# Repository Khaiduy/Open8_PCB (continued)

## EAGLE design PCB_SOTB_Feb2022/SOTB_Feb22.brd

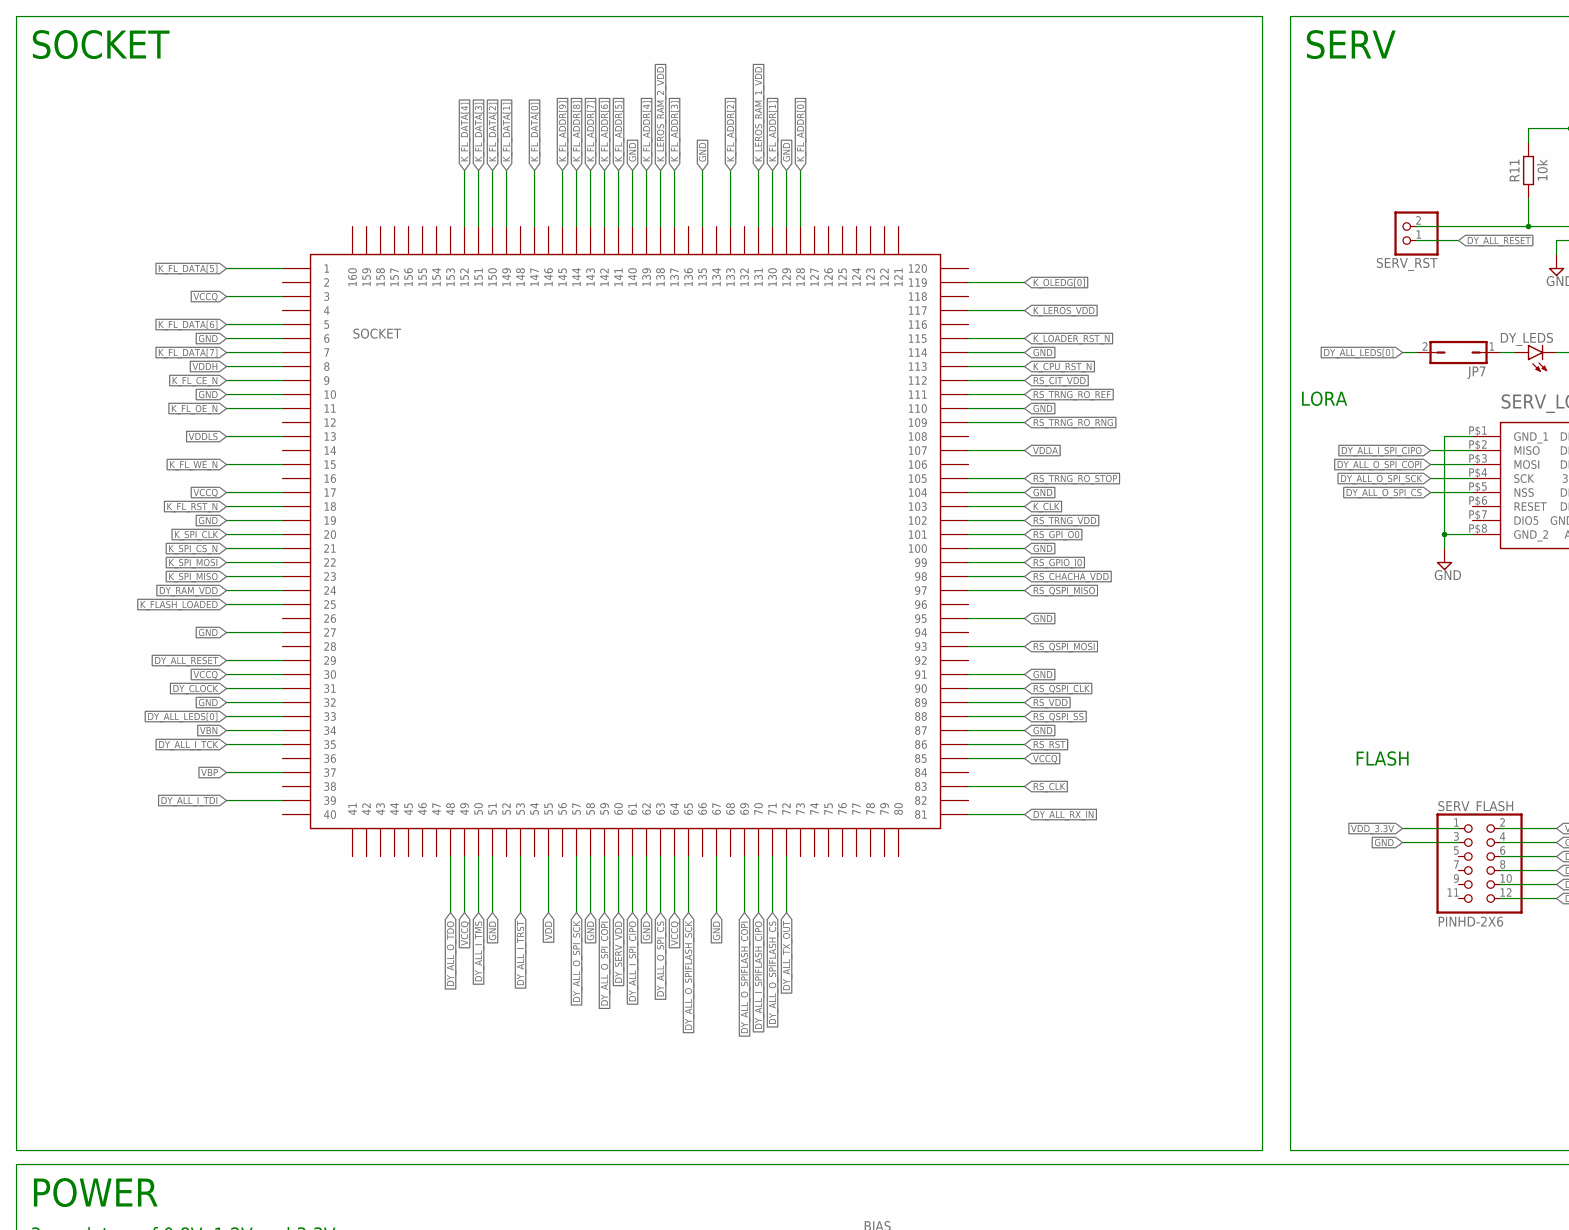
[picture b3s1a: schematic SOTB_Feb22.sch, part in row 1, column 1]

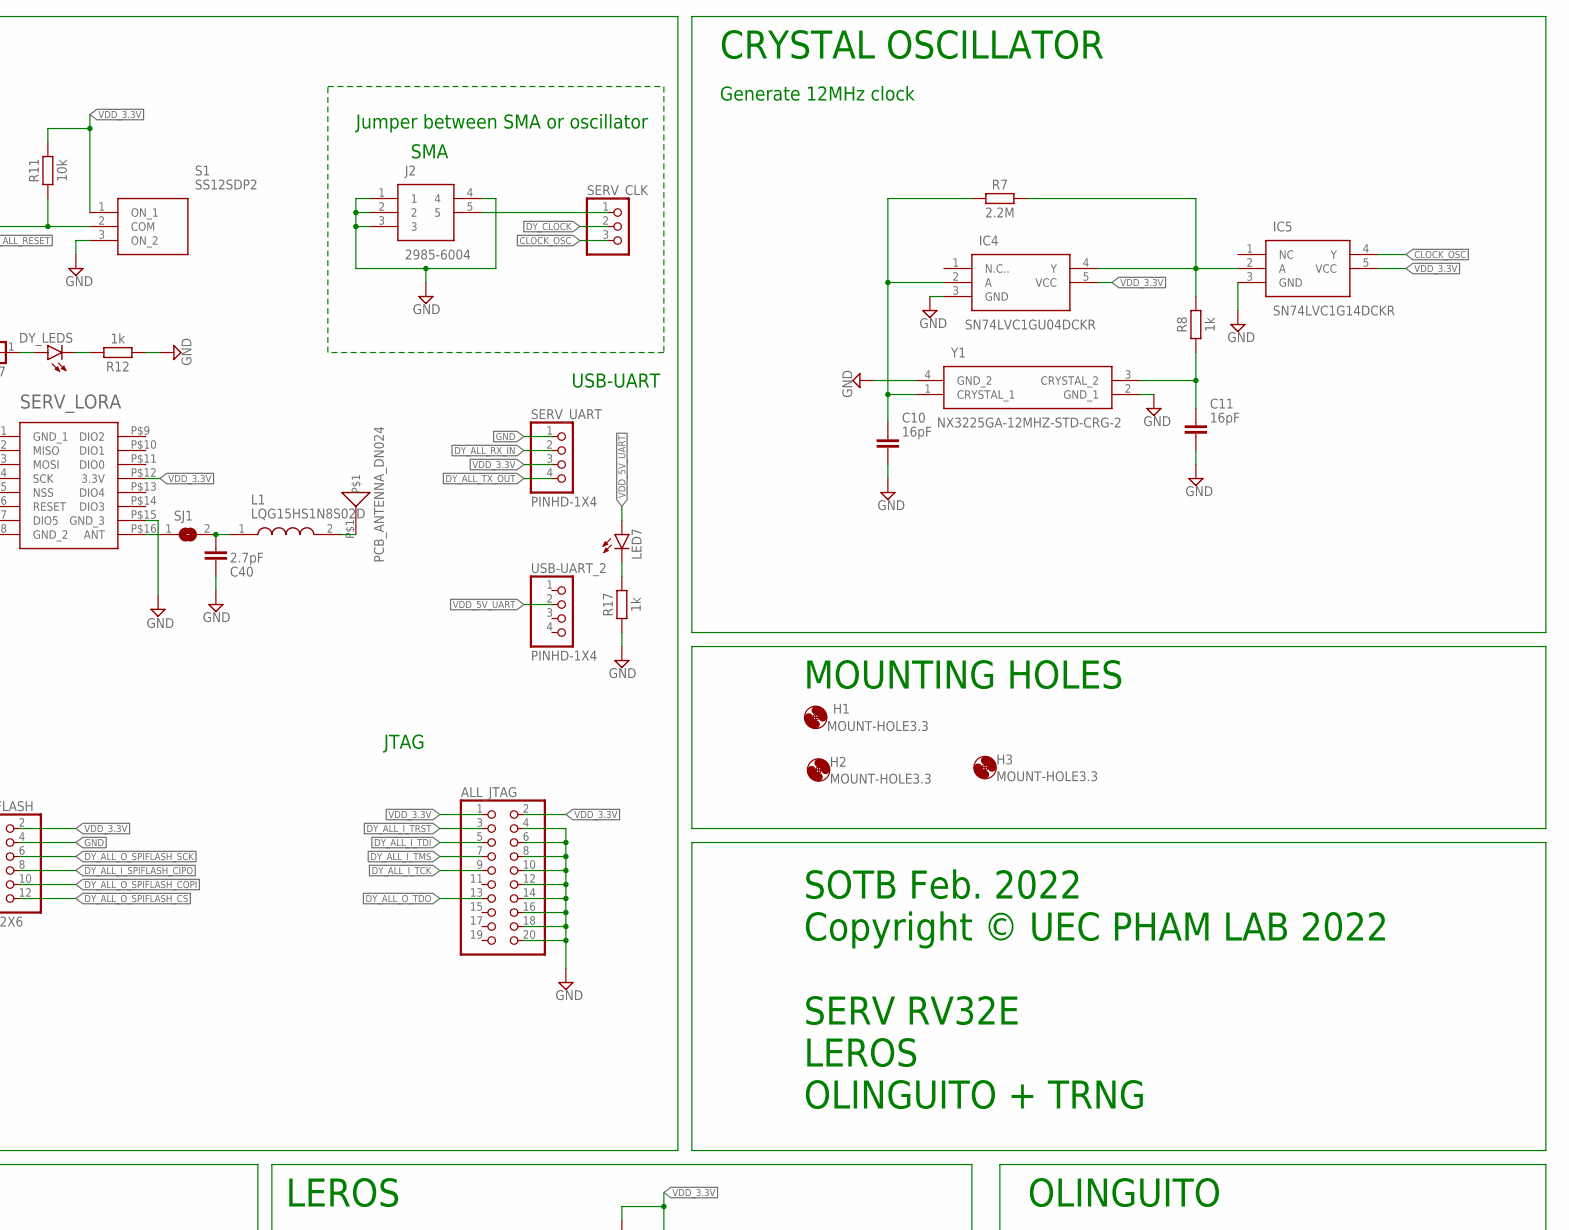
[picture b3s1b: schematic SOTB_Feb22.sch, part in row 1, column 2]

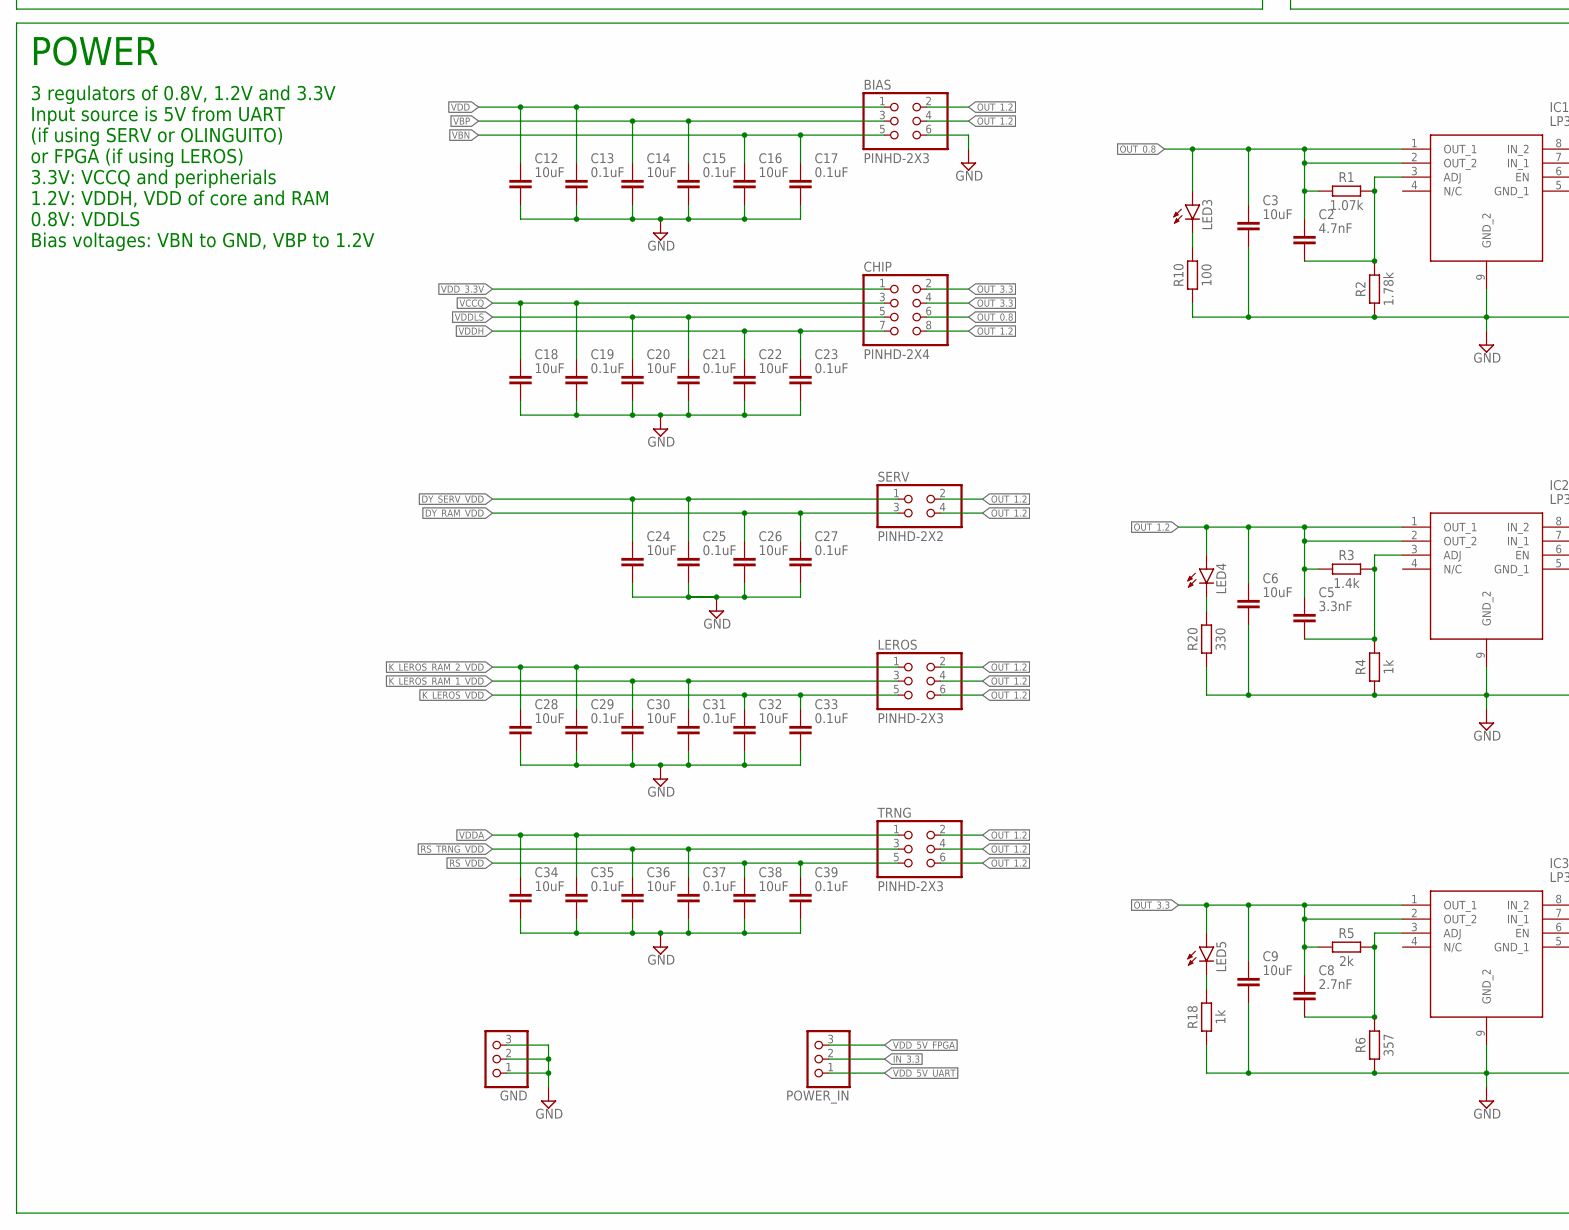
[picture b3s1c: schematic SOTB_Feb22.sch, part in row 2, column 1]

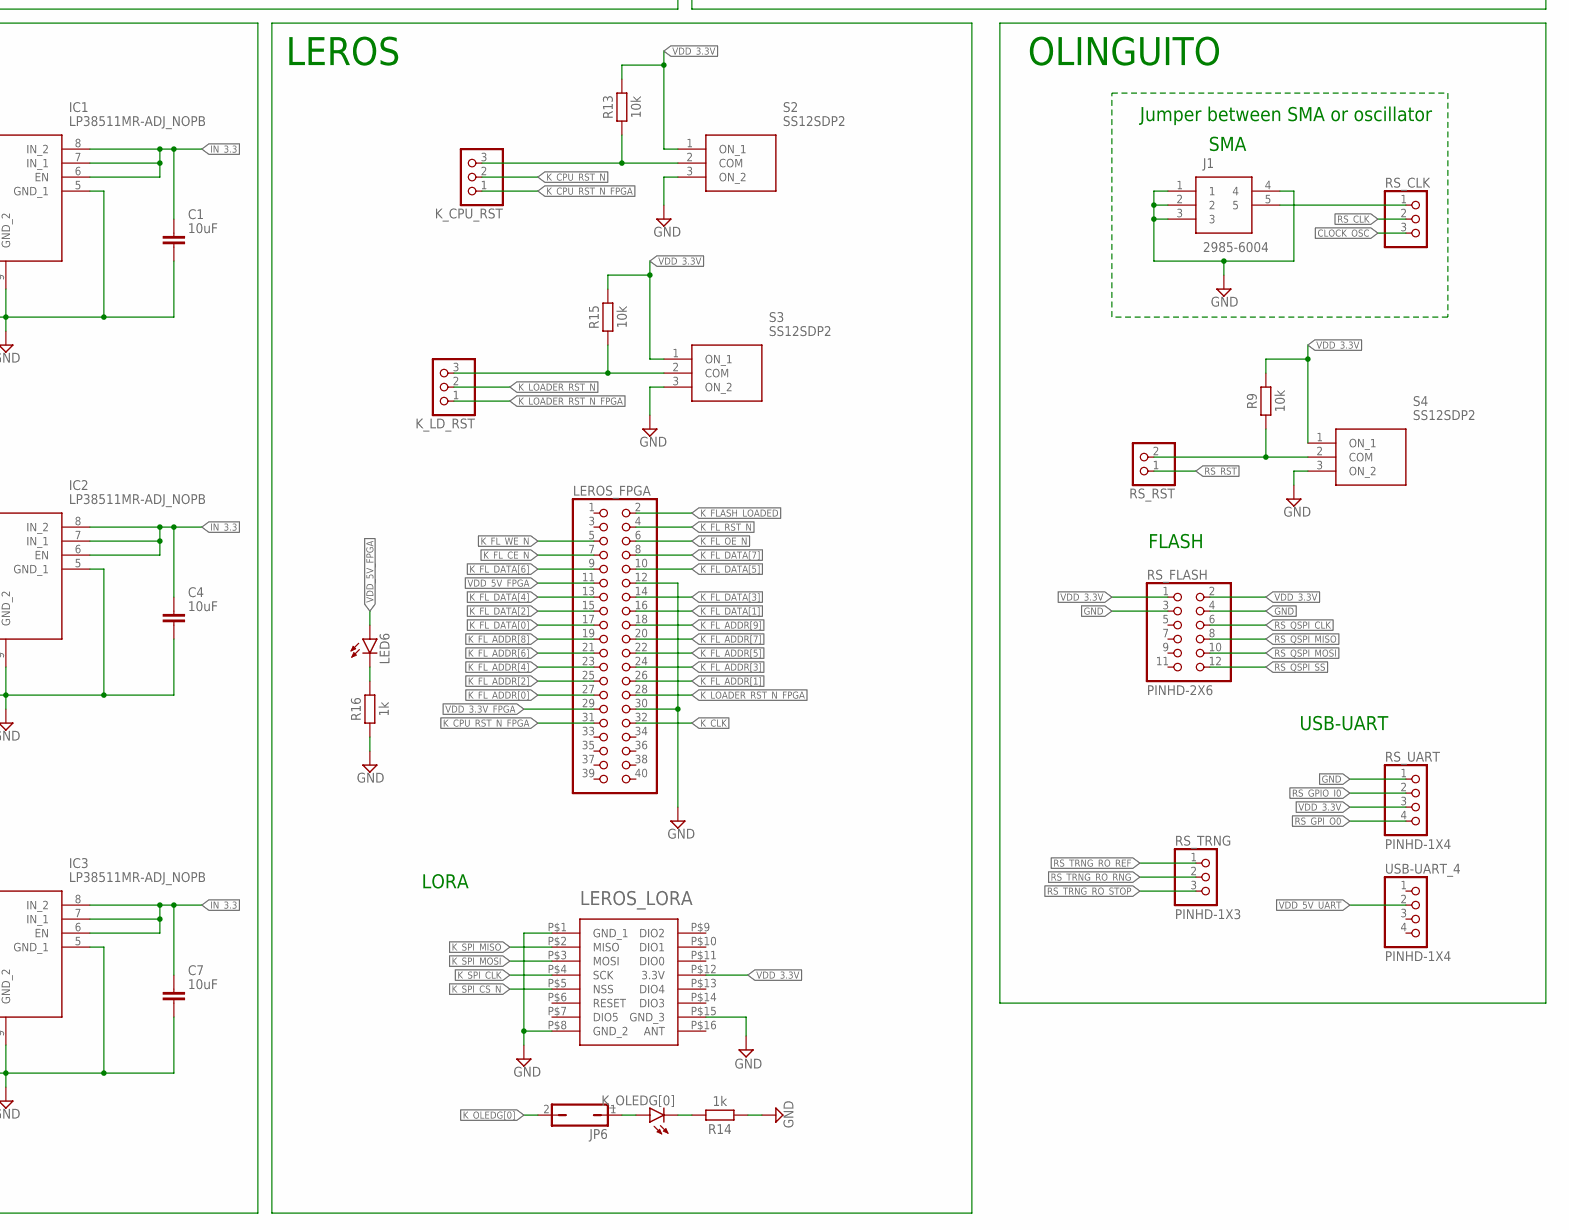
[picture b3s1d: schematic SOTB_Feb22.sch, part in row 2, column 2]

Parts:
ALL_JTAG: PINHD-2X10; 2X10
BIAS: PINHD-2X3; 2X03
C1, C3, C4, C6, C7, C9, C12, C14, C16, C18, C20, C22, C24, C26, C28, C30, C32, C34, C36, C38: 10uF; CAPC3216X135
C2: 4.7nF; CAPC3216X135
C5: 3.3nF; CAPC3216X135
C8: 2.7nF; CAPC3216X135
C10, C11: 16pF; CAPC3216X135
C13, C15, C17, C19, C21, C23, C25, C27, C29, C31, C33, C35, C37, C39: 0.1uF; CAPC3216X135
C40: 2.7pF; CAPC3216X135
CHIP: PINHD-2X4; 2X04
DY_LEDS: LEDCHIPLED_1206; CHIPLED_1206
GND: PINHD-1X3; 1X03
H1, H2, H3: MOUNT-HOLE3.3; 3,3
IC1, IC2, IC3: LP38511MR-ADJ_NOPB; SOIC127P600X170-9N
IC4: SN74LVC1GU04DCKR; SOT65P210X110-5N
IC5: SN74LVC1G14DCKR; SOT65P210X110-5N
J1, J2: 2985-6004; 29856004
JP6, JP7: JP1Q; JP1
K_CPU_RST: PINHD-1X3; 1X03
K_LD_RST: PINHD-1X3; 1X03
K_OLEDG[0]: LEDCHIPLED_1206; CHIPLED_1206
L1: LQG15HS1N8S02D; LQG15WH0N7B02D
LED3, LED4, LED5, LED6, LED7: LEDCHIPLED_1206; CHIPLED_1206
LEROS: PINHD-2X3; 2X03
LEROS_FPGA: PINHD-2X20; 2X20
LEROS_LORA: RFM95W-915S2
POWER_IN: PINHD-1X3; 1X03
R1: 1.07k; RESC3216X70
R2: 1.78k; RESC3216X70
R3: 1.4k; RESC3216X70
R4, R8, R12, R14, R16, R17, R18: 1k; RESC3216X70
R5: 2k; RESC3216X70
R6: 357; RESC3216X70
R7: 2.2M; RESC3216X70
R9, R11, R13, R15: 10k; RESC3216X70
R10: 100; RESC3216X70
R20: 330; RESC3216X70
RS_CLK: PINHD-1X3; 1X03
RS_FLASH: PINHD-2X6; 2X06
RS_RST: PINHD-1X2; 1X02
RS_TRNG: PINHD-1X3; 1X03
RS_UART: PINHD-1X4; 1X04
S1, S2, S3, S4: SS12SDP2
SERV: PINHD-2X2; 2X02
SERV_CLK: PINHD-1X3; 1X03
SERV_FLASH: PINHD-2X6; 2X06
SERV_LORA: RFM95W-915S2
SERV_RST: PINHD-1X2; 1X02
SERV_UART: PINHD-1X4; 1X04
SJ1: SJ
SOCKET: QFP28-160PIN
TRNG: PINHD-2X3; 2X03
U$1: 868MHZA_ANTENNA_DN024; 868MHZ_ANTENNA_DN024
USB-UART_2, USB-UART_4: PINHD-1X4; 1X04
Y1: NX3225GA-12MHZ-STD-CRG-2; NX3225GA12MHZSTDCRG2

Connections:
CLOCK_OSC: IC5.4 (Y), RS_CLK.3, SERV_CLK.3
DY_ALL_I_SPIFLASH_CIPO: SERV_FLASH.8, SOCKET.P$70 (70)
DY_ALL_I_SPI_CIPO: SERV_LORA.P$2 (MISO), SOCKET.P$61 (61)
DY_ALL_I_TCK: ALL_JTAG.9, SOCKET.P$35 (35)
DY_ALL_I_TDI: ALL_JTAG.5, SOCKET.P$39 (39)
DY_ALL_I_TMS: ALL_JTAG.7, SOCKET.P$50 (50)
DY_ALL_I_TRST: ALL_JTAG.3, SOCKET.P$53 (53)
DY_ALL_LEDS[0]: JP7.2, SOCKET.P$33 (33)
DY_ALL_O_SPIFLASH_COPI: SERV_FLASH.10, SOCKET.P$69 (69)
DY_ALL_O_SPIFLASH_CS: SERV_FLASH.12, SOCKET.P$71 (71)
DY_ALL_O_SPIFLASH_SCK: SERV_FLASH.6, SOCKET.P$65 (65)
DY_ALL_O_SPI_COPI: SERV_LORA.P$3 (MOSI), SOCKET.P$59 (59)
DY_ALL_O_SPI_CS: SERV_LORA.P$5 (NSS), SOCKET.P$63 (63)
DY_ALL_O_SPI_SCK: SERV_LORA.P$4 (SCK), SOCKET.P$57 (57)
DY_ALL_O_TDO: ALL_JTAG.13, SOCKET.P$48 (48)
DY_ALL_RESET: SERV_RST.1, SOCKET.P$29 (29)
DY_ALL_RX_IN: SERV_UART.2, SOCKET.P$81 (81)
DY_ALL_TX_OUT: SERV_UART.4, SOCKET.P$72 (72)
DY_CLOCK: SERV_CLK.2, SOCKET.P$31 (31)
DY_RAM_VDD: C26.1, C27.1, SERV.3, SOCKET.P$24 (24)
DY_SERV_VDD: C24.1, C25.1, SERV.1, SOCKET.P$60 (60)
GND: ALL_JTAG.4, ALL_JTAG.6, ALL_JTAG.8, ALL_JTAG.10, ALL_JTAG.12, ALL_JTAG.14, ALL_JTAG.16, ALL_JTAG.18, ALL_JTAG.20, BIAS.6, C1.2, C3.2, C4.2, C6.2, C7.2, C9.2, C10.2, C11.2, C12.2, C13.2, C14.2, C15.2, C16.2, C17.2, C18.2, C19.2, C20.2, C21.2, C22.2, C23.2, C24.2, C25.2, C26.2, C27.2, C28.2, C29.2, C30.2, C31.2, C32.2, C33.2, C34.2, C35.2, C36.2, C37.2, C38.2, C39.2, C40.2, GND.1, GND.2, GND.3, IC1.5 (GND_1), IC1.9 (GND_2), IC2.5 (GND_1), IC2.9 (GND_2), IC3.5 (GND_1), IC3.9 (GND_2), IC4.3 (GND), IC5.3 (GND), J1.1, J1.2, J1.3, J1.4, J2.1, J2.2, J2.3, J2.4, LEROS_FPGA.12, LEROS_FPGA.30, LEROS_LORA.P$1 (GND_1), LEROS_LORA.P$8 (GND_2), LEROS_LORA.P$15 (GND_3), R2.1, R4.1, R6.1, R10.1, R12.1, R14.1, R16.1, R17.1, R18.1, R20.1, RS_FLASH.3, RS_FLASH.4, RS_UART.1, S1.3 (ON_2), S2.3 (ON_2), S3.3 (ON_2), S4.3 (ON_2), SERV_FLASH.3, SERV_FLASH.4, SERV_LORA.P$1 (GND_1), SERV_LORA.P$8 (GND_2), SERV_LORA.P$15 (GND_3), SERV_UART.1, SOCKET.P$6 (6), SOCKET.P$10 (10), SOCKET.P$19 (19), SOCKET.P$27 (27), SOCKET.P$32 (32), SOCKET.P$51 (51), SOCKET.P$58 (58), SOCKET.P$62 (62), SOCKET.P$67 (67), SOCKET.P$87 (87), SOCKET.P$91 (91), SOCKET.P$95 (95), SOCKET.P$100 (100), SOCKET.P$104 (104), SOCKET.P$110 (110), SOCKET.P$114 (114), SOCKET.P$129 (129), SOCKET.P$135 (135), SOCKET.P$140 (140), Y1.2 (GND_1), Y1.4 (GND_2)
IN_3.3: C1.1, C4.1, C7.1, IC1.6 (EN), IC1.7 (IN_1), IC1.8 (IN_2), IC2.6 (EN), IC2.7 (IN_1), IC2.8 (IN_2), IC3.6 (EN), IC3.7 (IN_1), IC3.8 (IN_2), POWER_IN.2
K_CLK: LEROS_FPGA.32, SOCKET.P$103 (103)
K_CPU_RST_N: K_CPU_RST.2, SOCKET.P$113 (113)
K_CPU_RST_N_FPGA: K_CPU_RST.1, LEROS_FPGA.31
K_FLASH_LOADED: LEROS_FPGA.2, SOCKET.P$25 (25)
K_FL_ADDR[0]: LEROS_FPGA.27, SOCKET.P$128 (128)
K_FL_ADDR[1]: LEROS_FPGA.26, SOCKET.P$130 (130)
K_FL_ADDR[2]: LEROS_FPGA.25, SOCKET.P$133 (133)
K_FL_ADDR[3]: LEROS_FPGA.24, SOCKET.P$137 (137)
K_FL_ADDR[4]: LEROS_FPGA.23, SOCKET.P$139 (139)
K_FL_ADDR[5]: LEROS_FPGA.22, SOCKET.P$141 (141)
K_FL_ADDR[6]: LEROS_FPGA.21, SOCKET.P$142 (142)
K_FL_ADDR[7]: LEROS_FPGA.20, SOCKET.P$143 (143)
K_FL_ADDR[8]: LEROS_FPGA.19, SOCKET.P$144 (144)
K_FL_ADDR[9]: LEROS_FPGA.18, SOCKET.P$145 (145)
K_FL_CE_N: LEROS_FPGA.7, SOCKET.P$9 (9)
K_FL_DATA[0]: LEROS_FPGA.17, SOCKET.P$147 (147)
K_FL_DATA[1]: LEROS_FPGA.16, SOCKET.P$149 (149)
K_FL_DATA[2]: LEROS_FPGA.15, SOCKET.P$150 (150)
K_FL_DATA[3]: LEROS_FPGA.14, SOCKET.P$151 (151)
K_FL_DATA[4]: LEROS_FPGA.13, SOCKET.P$152 (152)
K_FL_DATA[5]: LEROS_FPGA.10, SOCKET.P$1 (1)
K_FL_DATA[6]: LEROS_FPGA.9, SOCKET.P$5 (5)
K_FL_DATA[7]: LEROS_FPGA.8, SOCKET.P$7 (7)
K_FL_OE_N: LEROS_FPGA.6, SOCKET.P$11 (11)
K_FL_RST_N: LEROS_FPGA.4, SOCKET.P$18 (18)
K_FL_WE_N: LEROS_FPGA.5, SOCKET.P$15 (15)
K_LEROS_RAM_1_VDD: C30.1, C31.1, LEROS.3, SOCKET.P$131 (131)
K_LEROS_RAM_2_VDD: C28.1, C29.1, LEROS.1, SOCKET.P$138 (138)
K_LEROS_VDD: C32.1, C33.1, LEROS.5, SOCKET.P$117 (117)
K_LOADER_RST_N: K_LD_RST.2, SOCKET.P$115 (115)
K_LOADER_RST_N_FPGA: K_LD_RST.1, LEROS_FPGA.28
K_OLEDG[0]: JP6.2, SOCKET.P$119 (119)
K_SPI_CLK: LEROS_LORA.P$4 (SCK), SOCKET.P$20 (20)
K_SPI_CS_N: LEROS_LORA.P$5 (NSS), SOCKET.P$21 (21)
K_SPI_MISO: LEROS_LORA.P$2 (MISO), SOCKET.P$23 (23)
K_SPI_MOSI: LEROS_LORA.P$3 (MOSI), SOCKET.P$22 (22)
unnamed: C2.2, IC1.3 (ADJ), R1.2, R2.2
unnamed: C5.2, IC2.3 (ADJ), R3.2, R4.2
unnamed: C8.2, IC3.3 (ADJ), R5.2, R6.2
unnamed: C10.1, IC4.2 (A), R7.1, Y1.1 (CRYSTAL_1)
unnamed: IC4.4 (Y), IC5.2 (A), R7.2, R8.2
unnamed: K_OLEDG[0].C, R14.2
unnamed: DY_LEDS.C, R12.2
unnamed: C11.1, R8.1, Y1.3 (CRYSTAL_2)
unnamed: LED3.C, R10.2
unnamed: LED4.C, R20.2
unnamed: LED5.C, R18.2
unnamed: JP6.1, K_OLEDG[0].A
unnamed: DY_LEDS.A, JP7.1
unnamed: LED6.C, R16.2
unnamed: LED7.C, R17.2
unnamed: C40.1, L1.1, SJ1.2
unnamed: L1.2, U$1.P$1
unnamed: SERV_LORA.P$16 (ANT), SJ1.1
OUT_0.8: C2.1, C3.1, CHIP.6, IC1.1 (OUT_1), IC1.2 (OUT_2), LED3.A, R1.1
OUT_1.2: BIAS.2, BIAS.4, C5.1, C6.1, CHIP.8, IC2.1 (OUT_1), IC2.2 (OUT_2), LED4.A, LEROS.2, LEROS.4, LEROS.6, R3.1, SERV.2, SERV.4, TRNG.2, TRNG.4, TRNG.6
OUT_3.3: C8.1, C9.1, CHIP.2, CHIP.4, IC3.1 (OUT_1), IC3.2 (OUT_2), LED5.A, R5.1
RST_SW: R11.1, S1.2 (COM), SERV_RST.2
RST_SW1: K_CPU_RST.3, R13.1, S2.2 (COM)
RST_SW2: K_LD_RST.3, R15.1, S3.2 (COM)
RST_SW3: R9.1, RS_RST.2, S4.2 (COM)
RS_CHACHA_VDD: SOCKET.P$98 (98)
RS_CIT_VDD: SOCKET.P$112 (112)
RS_CLK: RS_CLK.2, SOCKET.P$83 (83)
RS_GPIO_I0: RS_UART.2, SOCKET.P$99 (99)
RS_GPI_O0: RS_UART.4, SOCKET.P$101 (101)
RS_QSPI_CLK: RS_FLASH.6, SOCKET.P$90 (90)
RS_QSPI_MISO: RS_FLASH.8, SOCKET.P$97 (97)
RS_QSPI_MOSI: RS_FLASH.10, SOCKET.P$93 (93)
RS_QSPI_SS: RS_FLASH.12, SOCKET.P$88 (88)
RS_RST: RS_RST.1, SOCKET.P$86 (86)
RS_TRNG_RO_REF: RS_TRNG.1, SOCKET.P$111 (111)
RS_TRNG_RO_RNG: RS_TRNG.2, SOCKET.P$109 (109)
RS_TRNG_RO_STOP: RS_TRNG.3, SOCKET.P$105 (105)
RS_TRNG_VDD: C36.1, C37.1, SOCKET.P$102 (102), TRNG.3
RS_VDD: C38.1, C39.1, SOCKET.P$89 (89), TRNG.5
SMA_CLK: J2.5, SERV_CLK.1
SMA_CLK1: J1.5, RS_CLK.1
VBN: BIAS.5, C16.1, C17.1, SOCKET.P$34 (34)
VBP: BIAS.3, C14.1, C15.1, SOCKET.P$37 (37)
VCCQ: C18.1, C19.1, CHIP.3, SOCKET.P$3 (3), SOCKET.P$17 (17), SOCKET.P$30 (30), SOCKET.P$49 (49), SOCKET.P$64 (64), SOCKET.P$85 (85)
VDD: BIAS.1, C12.1, C13.1, SOCKET.P$55 (55)
VDDA: C34.1, C35.1, SOCKET.P$107 (107), TRNG.1
VDDH: C22.1, C23.1, CHIP.7, SOCKET.P$8 (8)
VDDLS: C20.1, C21.1, CHIP.5, SOCKET.P$13 (13)
VDD_3.3V: ALL_JTAG.1, ALL_JTAG.2, CHIP.1, IC4.5 (VCC), IC5.5 (VCC), LEROS_LORA.P$12 (3.3V), R9.2, R11.2, R13.2, R15.2, RS_FLASH.1, RS_FLASH.2, RS_UART.3, S1.1 (ON_1), S2.1 (ON_1), S3.1 (ON_1), S4.1 (ON_1), SERV_FLASH.1, SERV_FLASH.2, SERV_LORA.P$12 (3.3V), SERV_UART.3
VDD_3.3V_FPGA: LEROS_FPGA.29
VDD_5V_FPGA: LED6.A, LEROS_FPGA.11, POWER_IN.3
VDD_5V_UART: LED7.A, POWER_IN.1, USB-UART_2.2, USB-UART_4.2

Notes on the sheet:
SMA
FLASH
LORA
USB-UART
JTAG
POWER
SOCKET
SERV
CRYSTAL OSCILLATOR
LEROS
OLINGUITO
3 regulators of 0.8V, 1.2V and 3.3V Input source is 5V from UART (if using SERV or OLINGUITO) or FPGA (if using LEROS) 3.3V: VCCQ and peripherials 1.2V: VDDH, VDD of core and RAM 0.8V: VDDLS Bias voltages: VBN to GND, VBP to 1.2V
SOTB Feb. 2022 Copyright © UEC PHAM LAB 2022 SERV RV32E LEROS OLINGUITO + TRNG
MOUNTING HOLES
Generate 12MHz clock
Jumper between SMA or oscillator

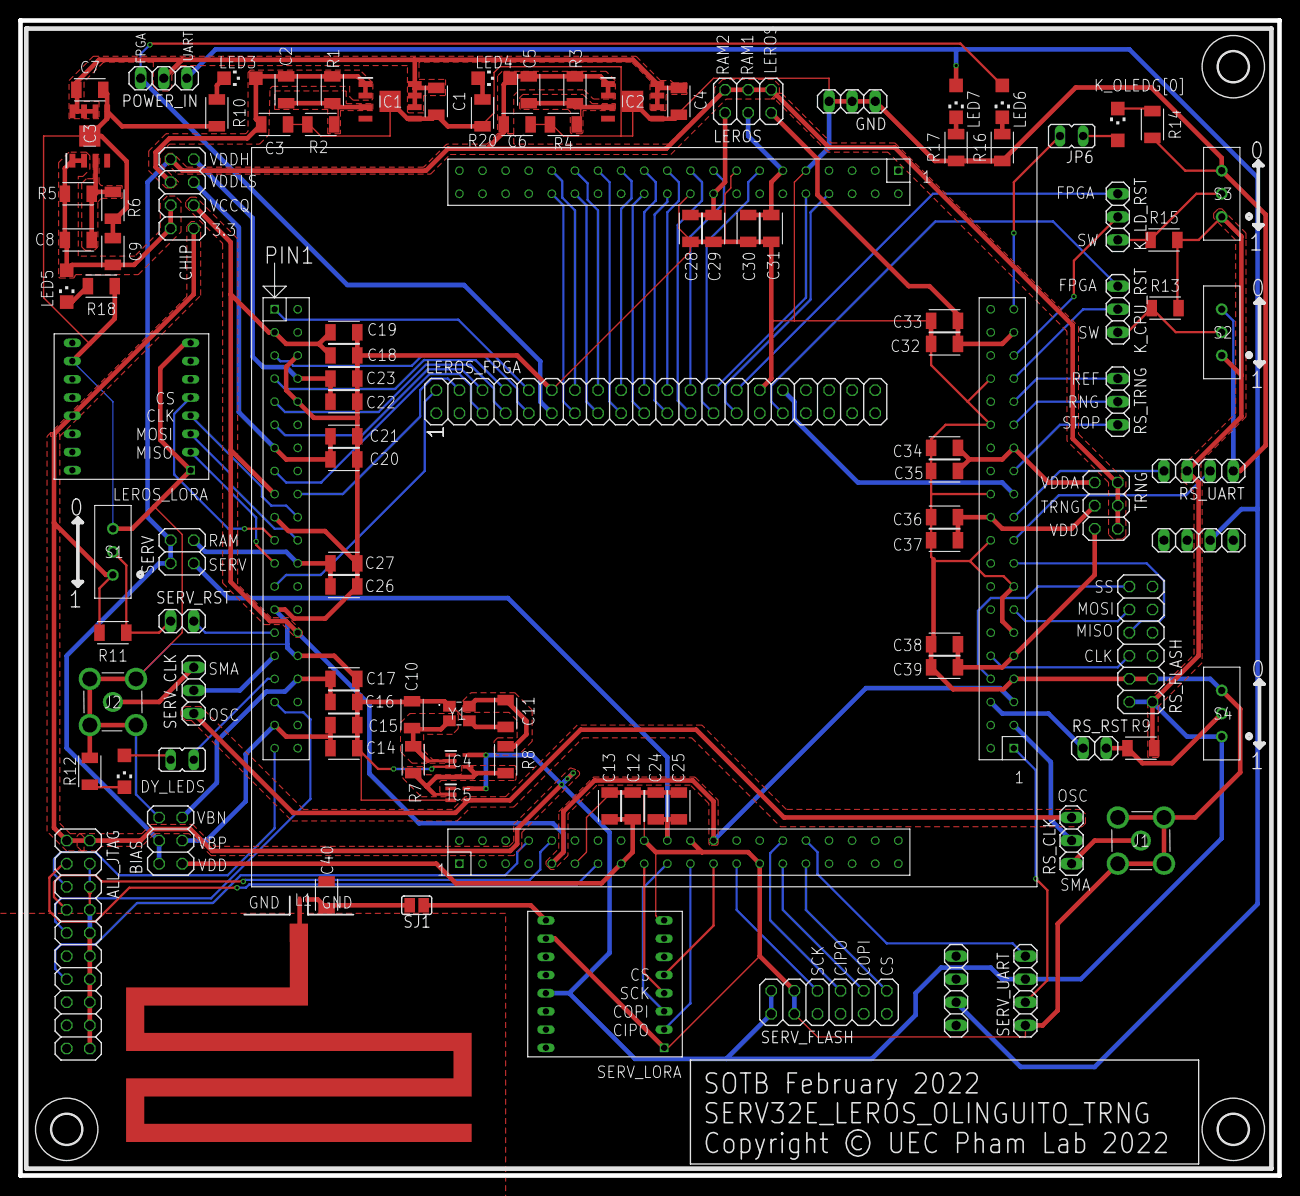
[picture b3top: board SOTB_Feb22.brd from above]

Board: 2 copper layers, 138.4 x 127.0 mm, 111 parts (0 on the bottom side), 109 nets.
